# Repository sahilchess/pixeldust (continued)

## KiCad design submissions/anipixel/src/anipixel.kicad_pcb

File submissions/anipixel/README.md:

---
name: "Chengyin Yao"
slack_id: "U07EQJY9YDD"
github_handle: "@cheyao"
tutorial: # Link to the tutorial if you used one, including the default guide
wokwi: https://wokwi.com/projects/428567150311352321
---

# Anipixel!

I'm calling it anipixel because why not lol.

Wokwi sim works: [https://wokwi.com/projects/428567150311352321](https://wokwi.com/projects/428567150311352321)

This was a nice kicad project, speedran it! Was super easy

Replace the wokwi link below with yours

⚠️ I can't smd solder, so I would need a soldering station

<!-- Example: -->

| Comment           | Quantity | LCSC     | Cost   |
|-------------------|----------|----------|--------|
| 10uF              | 4        | C15850   | 0.01$ |
| 100nF             | 9        | C49678   | 0.45$ |
| USB receptacle    | 1        | C3020560 | 1.09$ |
| Inductor 2.2uF    | 1        | C135262  | 0.51$ |
| 100  resistor     | 1        | C105577  | 0.21$ |
| 5.1k resistor     | 2        | C2930296 | 0.14$ |
| TPS63001          | 1        | C28060   | 2.72$ |
| WS2812B           | 8        |          | |
| ESP32-WROOM-32E   | 1        |          | |

Would also need $ to cover shipping please!

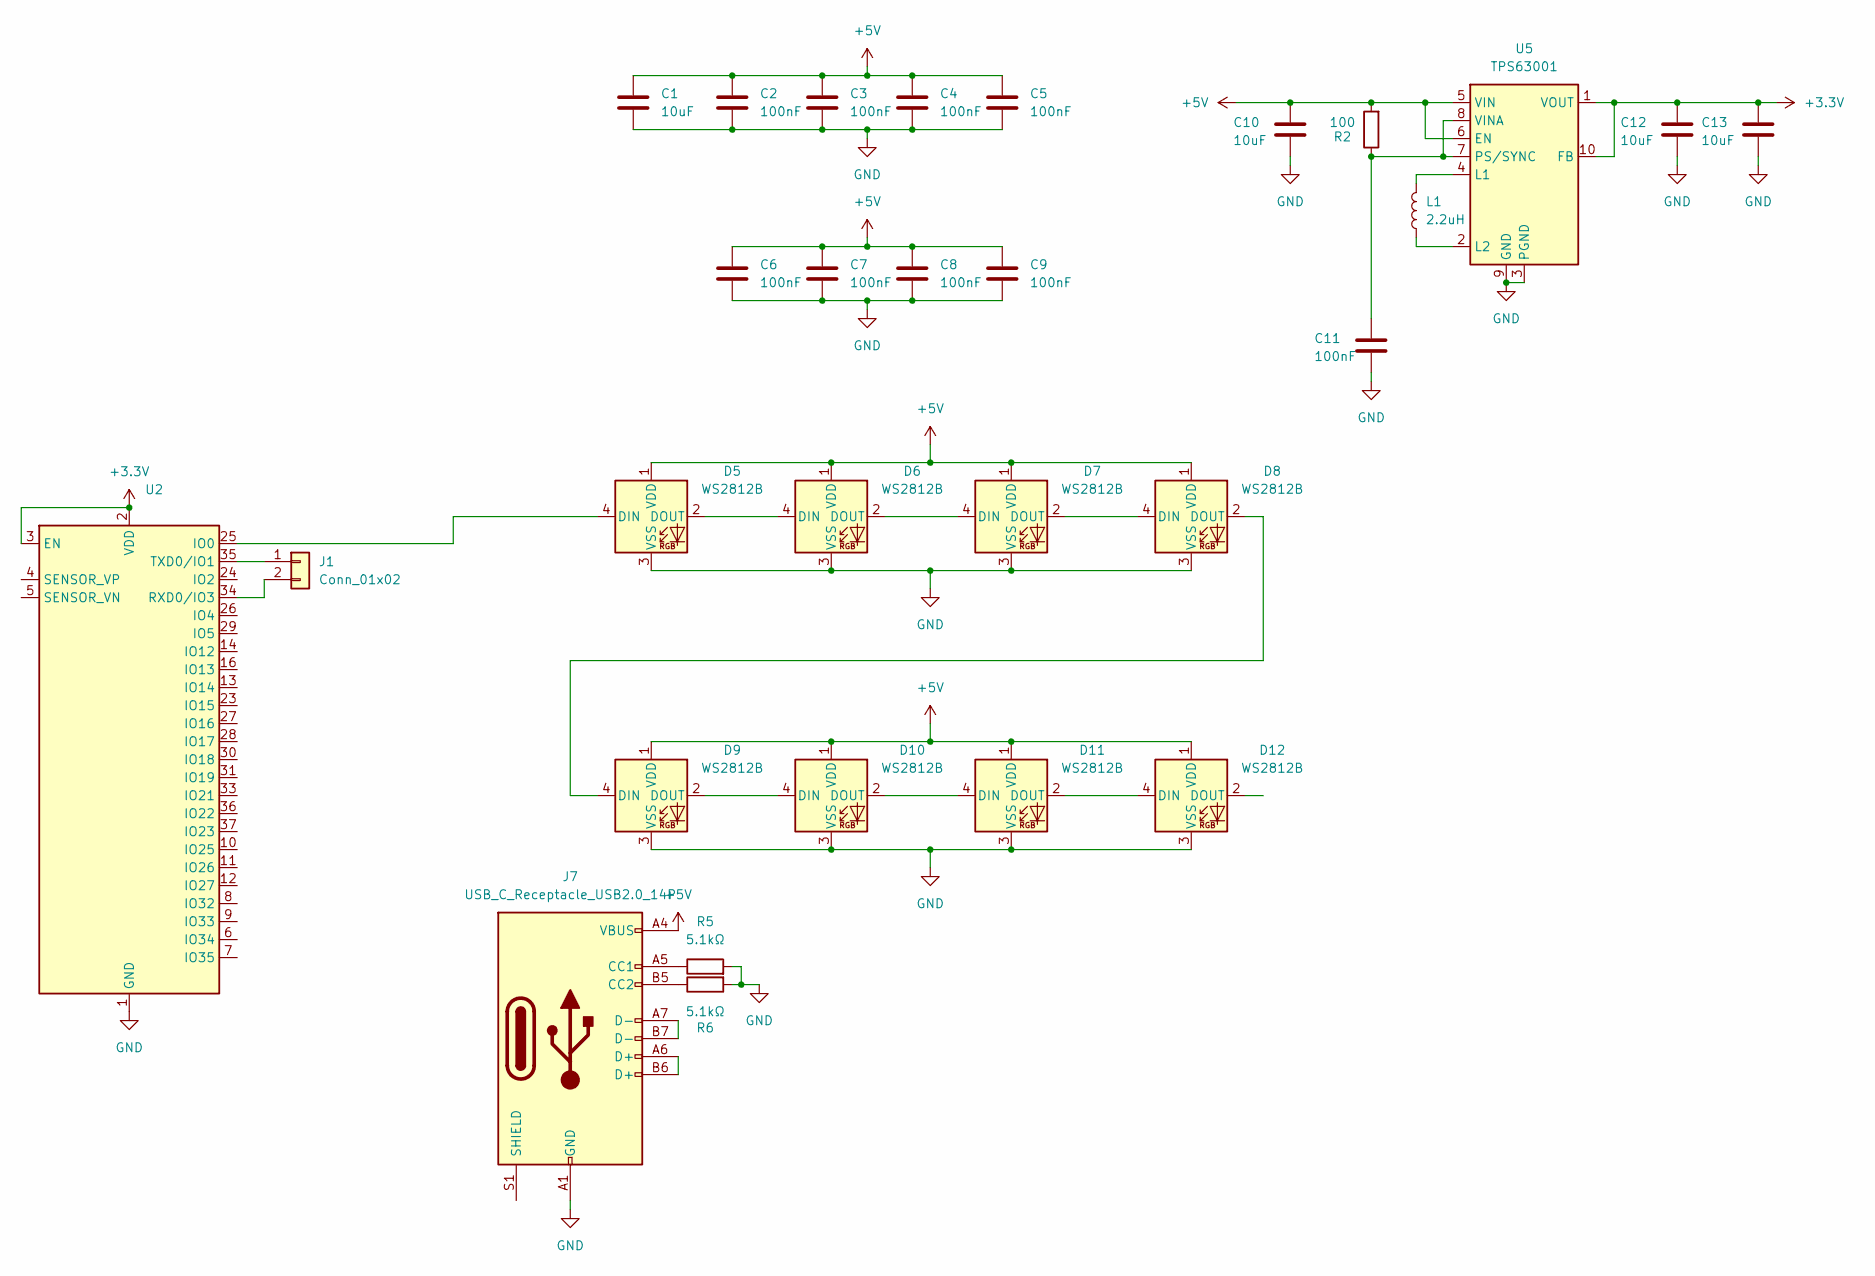
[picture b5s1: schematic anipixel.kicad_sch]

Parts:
C1, C10, C12, C13: 10uF; C_0805_2012Metric_Pad1.18x1.45mm_HandSolder
C2, C3, C4, C5, C6, C7, C8, C9, C11: 100nF; C_0805_2012Metric_Pad1.18x1.45mm_HandSolder
D5, D6, D7, D8, D9, D10, D11, D12: WS2812B; LED_WS2812B_PLCC4_5.0x5.0mm_P3.2mm
J1: Conn_01x02; PinHeader_1x02_P2.54mm_Vertical
J7: USB_C_Receptacle_USB2.0_14P; USB_C_Receptacle_GCT_USB4105-xx-A_16P_TopMnt_Horizontal
L1: 2.2uH; NR3015T2R2M
R2: 100; R_0805_2012Metric_Pad1.20x1.40mm_HandSolder
R5, R6: 5.1kΩ; R_0805_2012Metric_Pad1.20x1.40mm_HandSolder
U2: ESP32-WROOM-32E; ESP32-WROOM-32D
U5: TPS63001; Texas_DRC0010J_ThermalVias

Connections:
+3.3V: C12.1, C13.1, U2.2 (VDD), U2.3 (EN), U5.1 (VOUT), U5.10 (FB)
+5V: C1.1, C2.1, C3.1, C4.1, C5.1, C6.1, C7.1, C8.1, C9.1, C10.1, D5.1 (VDD), D6.1 (VDD), D7.1 (VDD), D8.1 (VDD), D9.1 (VDD), D10.1 (VDD), D11.1 (VDD), D12.1 (VDD), J7.A4 (VBUS), J7.A9 (VBUS), J7.B4 (VBUS), J7.B9 (VBUS), R2.2, U5.5 (VIN), U5.6 (EN)
GND: C1.2, C2.2, C3.2, C4.2, C5.2, C6.2, C7.2, C8.2, C9.2, C10.2, C11.2, C12.2, C13.2, D5.3 (VSS), D6.3 (VSS), D7.3 (VSS), D8.3 (VSS), D9.3 (VSS), D10.3 (VSS), D11.3 (VSS), D12.3 (VSS), J7.A1 (GND), J7.A12 (GND), J7.B1 (GND), J7.B12 (GND), R5.2, R6.2, U2.1 (GND), U2.15 (GND), U2.38 (GND), U2.39 (GND), U5.3 (PGND), U5.9 (GND), U5.11 (PGND)
unnamed: D5.4 (DIN), U2.25 (IO0)
unnamed: D5.2 (DOUT), D6.4 (DIN)
unnamed: D6.2 (DOUT), D7.4 (DIN)
unnamed: D7.2 (DOUT), D8.4 (DIN)
unnamed: D8.2 (DOUT), D9.4 (DIN)
unnamed: D9.2 (DOUT), D10.4 (DIN)
unnamed: D10.2 (DOUT), D11.4 (DIN)
unnamed: D11.2 (DOUT), D12.4 (DIN)
unnamed: J1.1, U2.35 (TXD0/IO1)
unnamed: J1.2, U2.34 (RXD0/IO3)
unnamed: J7.A5 (CC1), R5.1
unnamed: J7.B5 (CC2), R6.1
unnamed: J7.A6 (D+), J7.B6 (D+)
unnamed: J7.A7 (D-), J7.B7 (D-)
unnamed: L1.2, U5.4 (L1)
unnamed: L1.1, U5.2 (L2)
unnamed: C11.1, R2.1, U5.7 (PS/SYNC), U5.8 (VINA)

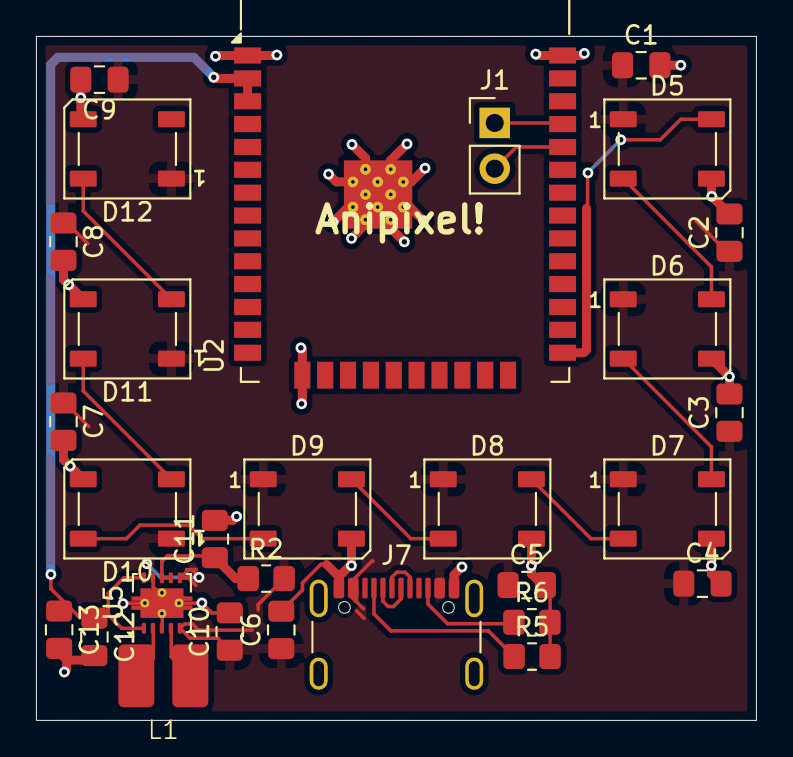
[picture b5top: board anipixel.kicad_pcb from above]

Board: 2 copper layers, 40.0 x 38.0 mm, 29 parts (0 on the bottom side), 20 nets.

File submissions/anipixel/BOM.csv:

Designator,Footprint,Quantity,Value,LCSC Part #
C1,0805,1,10u,
"C10, C12, C13",0805,3,10uF,
C11,0805,1,0.1uF,
"C2, C3, C4, C5, C6, C7, C8, C9",0805,8,100n,
"D10, D11, D12, D5, D6, D7, D8, D9",LED_WS2812B_PLCC4_5.0x5.0mm_P3.2mm,8,WS2812B,
J7,USB_C_Receptacle_GCT_USB4105-xx-A_16P_TopMnt_Horizontal,1,USB_C_Receptacle_USB2.0_14P,
L1,NR3015T2R2M,1,2.2uH,
R2,0805,1,100,
"R5, R6",0805,2,5.1kΩ,
U2,ESP32-WROOM-32D,1,ESP32-WROOM-32E,
U5,Texas_DRC0010J_ThermalVias,1,TPS63001,

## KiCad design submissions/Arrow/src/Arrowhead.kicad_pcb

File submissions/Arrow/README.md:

---
name: "SUKHDEEP SOMAL"
slack_id: "T0266FRGM"
github_handle: "@TwistedMiraculous"

wokwi: # Link to the Wokwi project
---

# Arrow head trinket

Wokwi link: [https://wokwi.com/projects/428801189855389697](https://wokwi.com/projects/428801189855389697)

Describe your board in 2-3 sentences. What are you making? What will it do?
I have made an led charm to make it either into a lightup bracelet, keychain, or a necklace. I will try to make a case for it but for now I want to keep it as it is, to show off that I made something.

A simplified BOM table

| Comment           | Footprint                                      | Quantity | LCSC     | Cost   |
|-------------------|------------------------------------------------|----------|----------|--------|
| 100uF             | Capacitor_SMD:CP_Elec_6.3x7.7                  | 1        | C15008   | 0.0682$|
| 0.1uF             | Capacitor_SMD:C_0603_1608Metric                | 7        | C1538    | 0.0011$|
| SK6812MINI        | LED_SMD:LED_SK6812MINI_PLCC4_3.5x3.5mm_P1.75mm | 8        | C1538    | 0.0726$|
| 330Ω              | Resistor_SMD:R_0402_1005Metric                 | 1        | C25091   | 0.0006$|
| XIAO-RP2040-DIP   | XIAO-RP2040-DIP                                | 1        |          | $5-8   |

Tell us a little bit about your design process. What were some challenges? What helped?

Some images of your design (make sure to include both the PCB and Schematic!):
,

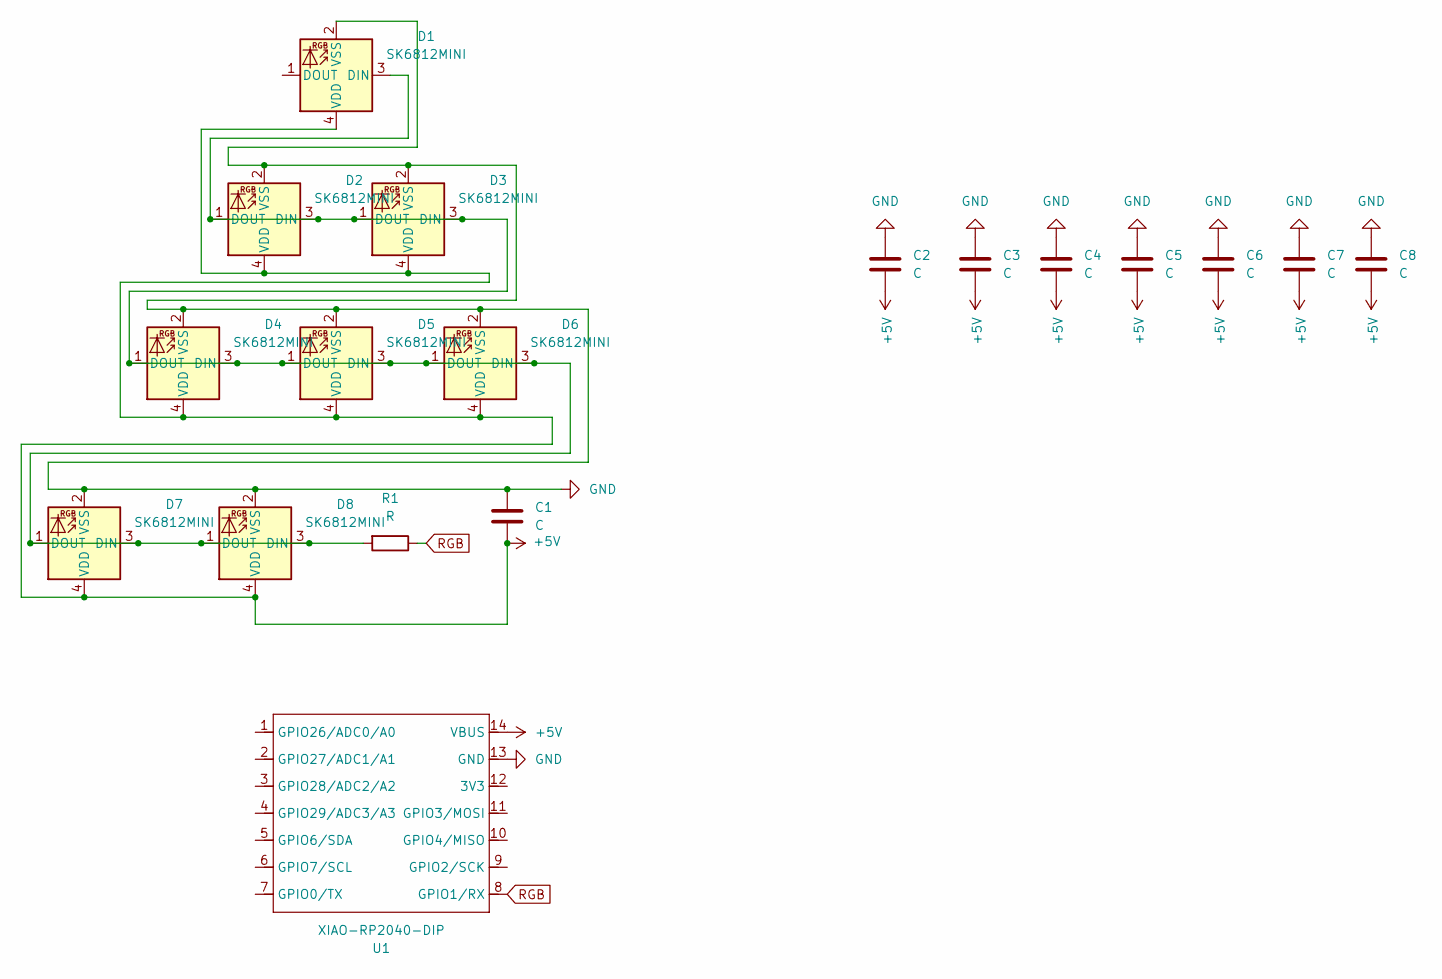
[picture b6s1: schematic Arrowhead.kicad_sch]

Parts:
C1: C; CP_Elec_6.3x7.7
C2, C3, C4, C5, C6, C7, C8: C; C_0603_1608Metric
D1, D2, D3, D4, D5, D6, D7, D8: SK6812MINI; LED_SK6812MINI_PLCC4_3.5x3.5mm_P1.75mm
R1: R; R_0402_1005Metric
U1: XIAO-RP2040-DIP

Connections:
+5V: C1.2, C2.2, C3.2, C4.2, C5.2, C6.2, C7.2, C8.2, D1.4 (VDD), D2.4 (VDD), D3.4 (VDD), D4.4 (VDD), D5.4 (VDD), D6.4 (VDD), D7.4 (VDD), D8.4 (VDD), U1.14 (VBUS)
GND: C1.1, C2.1, C3.1, C4.1, C5.1, C6.1, C7.1, C8.1, D1.2 (VSS), D2.2 (VSS), D3.2 (VSS), D4.2 (VSS), D5.2 (VSS), D6.2 (VSS), D7.2 (VSS), D8.2 (VSS), U1.13 (GND)
unnamed: D1.3 (DIN), D2.1 (DOUT), D2.3 (DIN), D3.1 (DOUT), D3.3 (DIN), D4.1 (DOUT), D4.3 (DIN), D5.1 (DOUT), D5.3 (DIN), D6.1 (DOUT), D6.3 (DIN), D7.1 (DOUT), D7.3 (DIN), D8.1 (DOUT), D8.3 (DIN), R1.2
RGB: R1.1, U1.8 (GPIO1/RX)

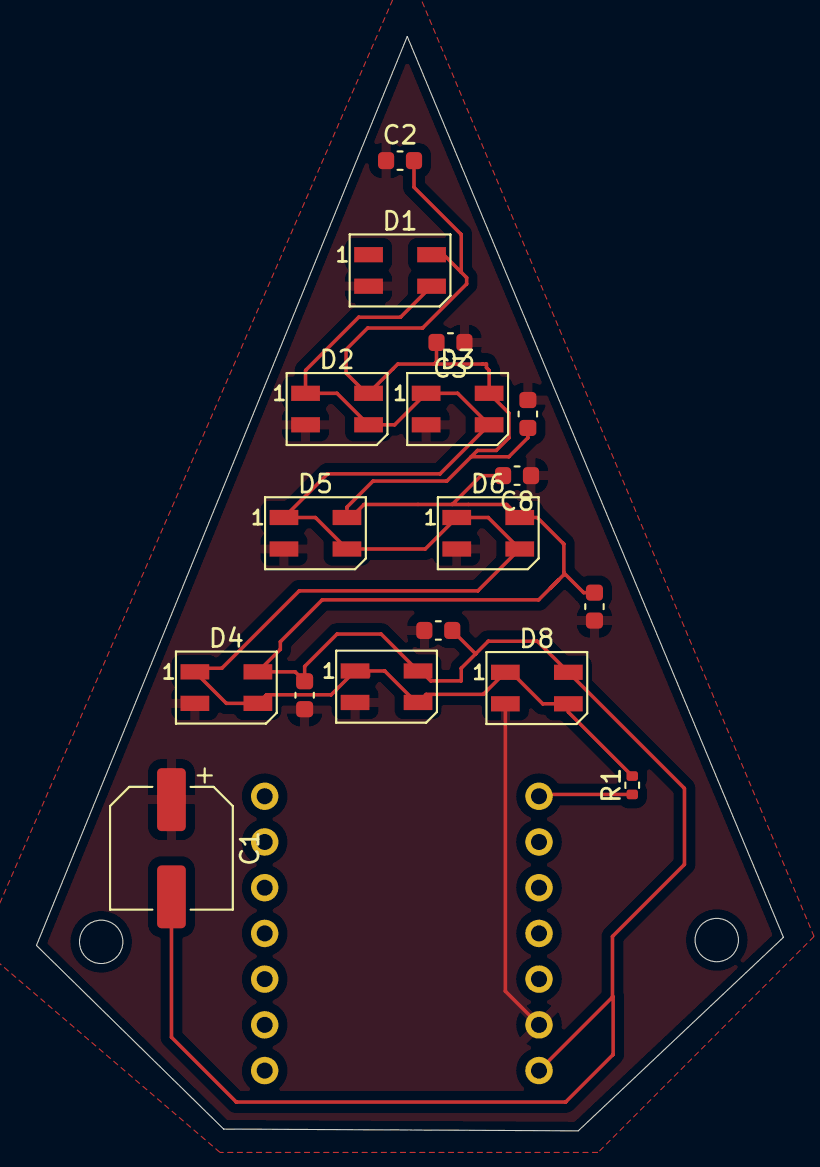
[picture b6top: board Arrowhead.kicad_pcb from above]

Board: 2 copper layers, 41.5 x 60.8 mm, 18 parts (1 on the bottom side), 4 nets.

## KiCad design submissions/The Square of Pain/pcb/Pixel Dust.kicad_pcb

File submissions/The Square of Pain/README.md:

# The Square of Pain

Jayson's slack ID: U085B15J7QW

Wokwi Link: https://wokwi.com/projects/427945974569788417
# Images

# PCB

# Schematic

# Model

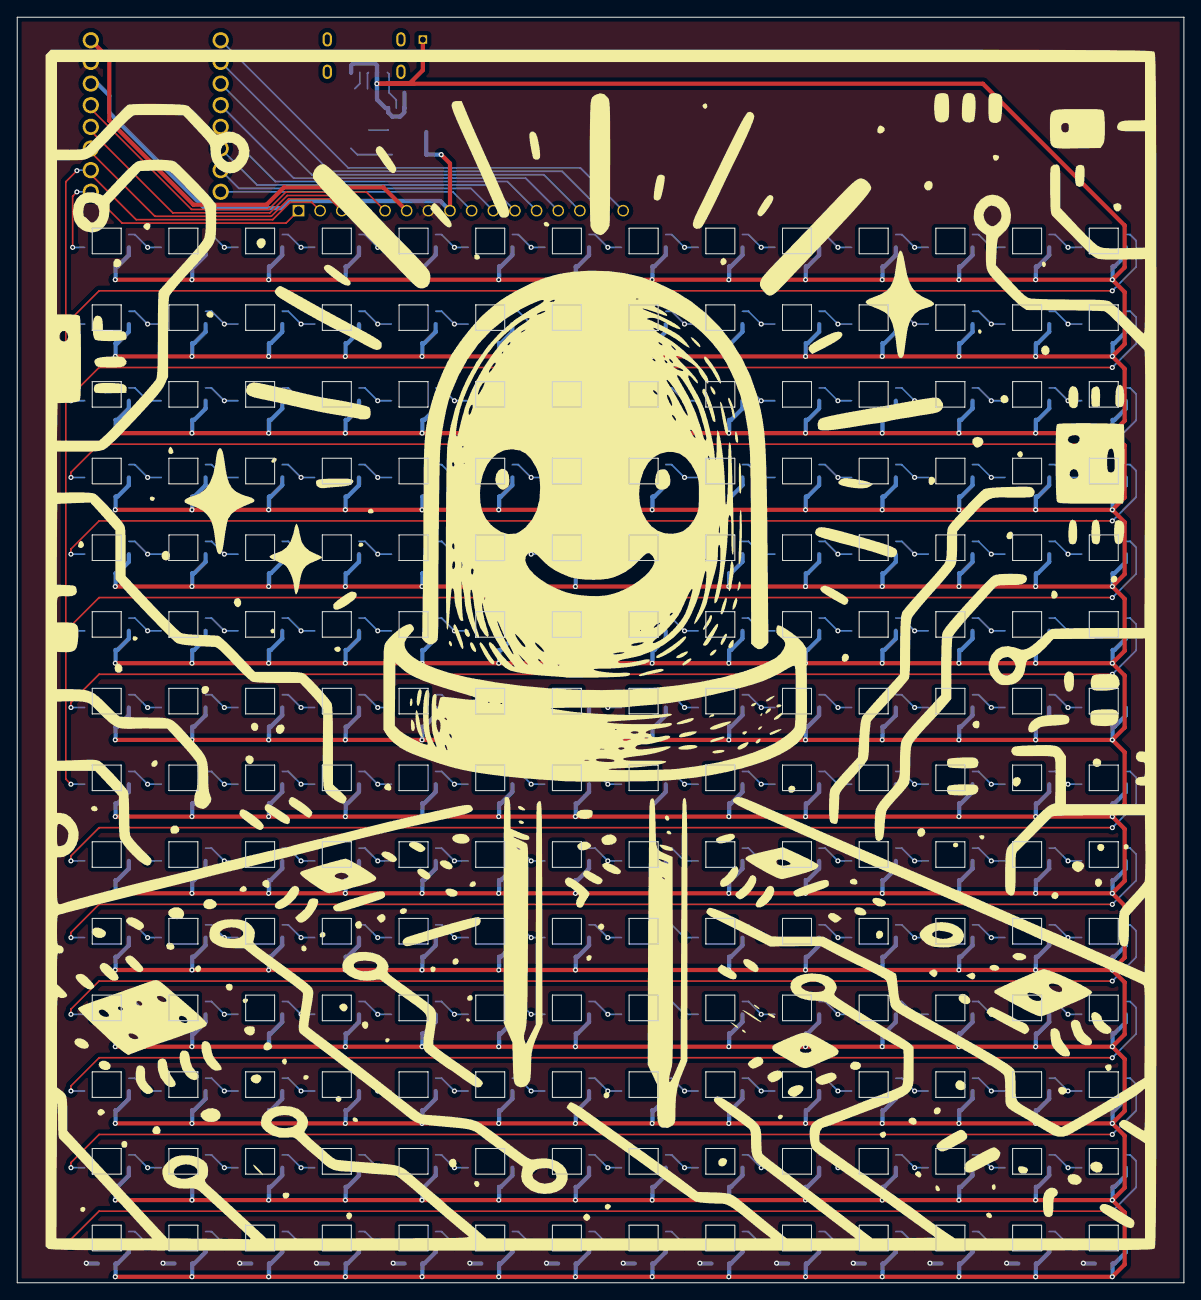
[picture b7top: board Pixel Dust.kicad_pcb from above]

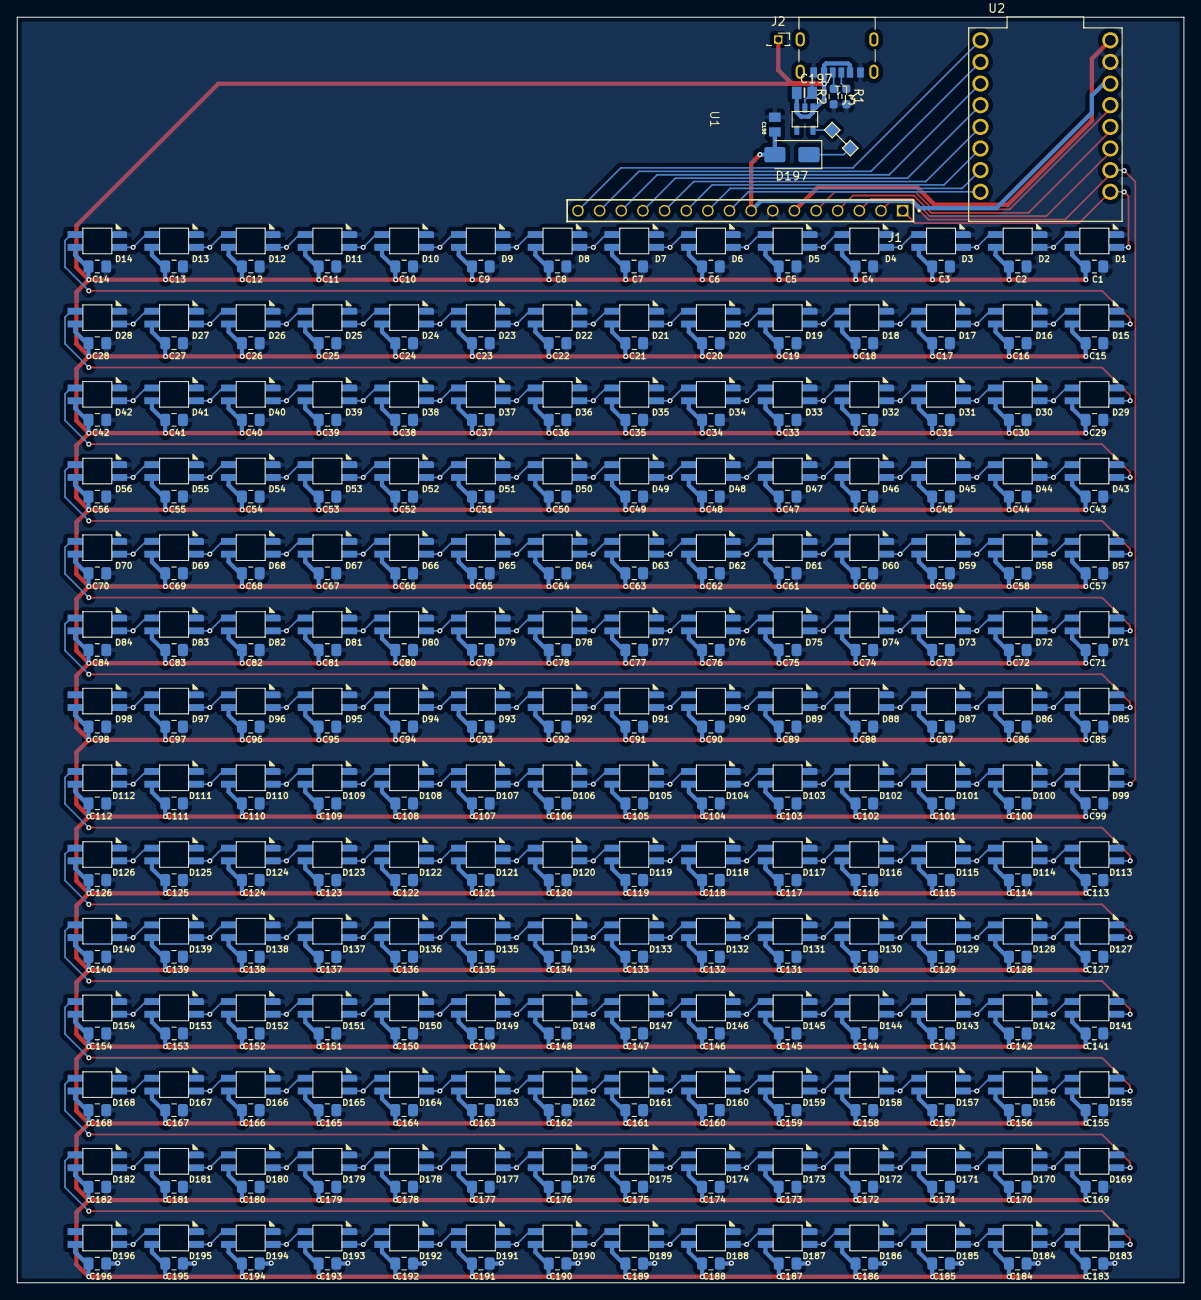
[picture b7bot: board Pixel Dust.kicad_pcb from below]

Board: 2 copper layers, 136.9 x 148.5 mm, 403 parts (403 on the bottom side), 215 nets.

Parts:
C1, C2, C3, C4, C5, C6, C7, C8, C9, C10, C11, C12, C13, C14, C15, C16, C17, C18, C19, C20, C21, C22, C23, C24, C25, C26, C27, C28, C29, C30, C31, C32, C33, C34, C35, C36, C37, C38, C39, C40, C41, C42, C43, C44, C45, C46, C47, C48, C49, C50, C51, C52, C53, C54, C55, C56, C57, C58, C59, C60, C61, C62, C63, C64, C65, C66, C67, C68, C69, C70, C71, C72, C73, C74, C75, C76, C77, C78, C79, C80, C81, C82, C83, C84, C85, C86, C87, C88, C89, C90, C91, C92, C93, C94, C95, C96, C97, C98, C99, C100, C101, C102, C103, C104, C105, C106, C107, C108, C109, C110, C111, C112, C113, C114, C115, C116, C117, C118, C119, C120, C121, C122, C123, C124, C125, C126, C127, C128, C129, C130, C131, C132, C133, C134, C135, C136, C137, C138, C139, C140, C141, C142, C143, C144, C145, C146, C147, C148, C149, C150, C151, C152, C153, C154, C155, C156, C157, C158, C159, C160, C161, C162, C163, C164, C165, C166, C167, C168, C169, C170, C171, C172, C173, C174, C175, C176, C177, C178, C179, C180, C181, C182, C183, C184, C185, C186, C187, C188, C189, C190, C191, C192, C193, C194, C195, C196: C; C_0805_2012Metric_Pad1.18x1.45mm_HandSolder
C197: 4.7 uF; CAPC2012X140N
C198: 10 uF; CAPC2012X135N
D1, D2, D3, D4, D5, D6, D7, D8, D9, D10, D11, D12, D13, D14, D15, D16, D17, D18, D19, D20, D21, D22, D23, D24, D25, D26, D27, D28, D29, D30, D31, D32, D33, D34, D35, D36, D37, D38, D39, D40, D41, D42, D43, D44, D45, D46, D47, D48, D49, D50, D51, D52, D53, D54, D55, D56, D57, D58, D59, D60, D61, D62, D63, D64, D65, D66, D67, D68, D69, D70, D71, D72, D73, D74, D75, D76, D77, D78, D79, D80, D81, D82, D83, D84, D85, D86, D87, D88, D89, D90, D91, D92, D93, D94, D95, D96, D97, D98, D99, D100, D101, D102, D103, D104, D105, D106, D107, D108, D109, D110, D111, D112, D113, D114, D115, D116, D117, D118, D119, D120, D121, D122, D123, D124, D125, D126, D127, D128, D129, D130, D131, D132, D133, D134, D135, D136, D137, D138, D139, D140, D141, D142, D143, D144, D145, D146, D147, D148, D149, D150, D151, D152, D153, D154, D155, D156, D157, D158, D159, D160, D161, D162, D163, D164, D165, D166, D167, D168, D169, D170, D171, D172, D173, D174, D175, D176, D177, D178, D179, D180, D181, D182, D183, D184, D185, D186, D187, D188, D189, D190, D191, D192, D193, D194, D195, D196: SK6812MINI; SK6812MINI-E
D197: SS14; D_SMA
J1: TSW-116-08-T-S-LL; SAMTEC_TSW-116-08-T-S-LL
J2: Conn_01x01_Socket; PinSocket_1x01_P1.27mm_Vertical
J3: USB_C_Receptacle_PowerOnly_6P; SAMESKY_UJC-H-G-SMT-2-P6-TR
L1: 2.2 uH; CDRH2D14NP-2R2NC
R1, R2: 5.1kΩ; R_0603_1608Metric_Pad0.98x0.95mm_HandSolder
U1: DC-DC_Converter
U2: ESP32-C3_SUPERMINI_TH; MODULE_ESP32-C3_SUPERMINI

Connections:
5V: J1.06, U2.5V
5in: C1.1, C2.1, C3.1, C4.1, C5.1, C6.1, C7.1, C8.1, C9.1, C10.1, C11.1, C12.1, C13.1, C14.1, C15.1, C16.1, C17.1, C18.1, C19.1, C20.1, C21.1, C22.1, C23.1, C24.1, C25.1, C26.1, C27.1, C28.1, C29.1, C30.1, C31.1, C32.1, C33.1, C34.1, C35.1, C36.1, C37.1, C38.1, C39.1, C40.1, C41.1, C42.1, C43.1, C44.1, C45.1, C46.1, C47.1, C48.1, C49.1, C50.1, C51.1, C52.1, C53.1, C54.1, C55.1, C56.1, C57.1, C58.1, C59.1, C60.1, C61.1, C62.1, C63.1, C64.1, C65.1, C66.1, C67.1, C68.1, C69.1, C70.1, C71.1, C72.1, C73.1, C74.1, C75.1, C76.1, C77.1, C78.1, C79.1, C80.1, C81.1, C82.1, C83.1, C84.1, C85.1, C86.1, C87.1, C88.1, C89.1, C90.1, C91.1, C92.1, C93.1, C94.1, C95.1, C96.1, C97.1, C98.1, C99.1, C100.1, C101.1, C102.1, C103.1, C104.1, C105.1, C106.1, C107.1, C108.1, C109.1, C110.1, C111.1, C112.1, C113.1, C114.1, C115.1, C116.1, C117.1, C118.1, C119.1, C120.1, C121.1, C122.1, C123.1, C124.1, C125.1, C126.1, C127.1, C128.1, C129.1, C130.1, C131.1, C132.1, C133.1, C134.1, C135.1, C136.1, C137.1, C138.1, C139.1, C140.1, C141.1, C142.1, C143.1, C144.1, C145.1, C146.1, C147.1, C148.1, C149.1, C150.1, C151.1, C152.1, C153.1, C154.1, C155.1, C156.1, C157.1, C158.1, C159.1, C160.1, C161.1, C162.1, C163.1, C164.1, C165.1, C166.1, C167.1, C168.1, C169.1, C170.1, C171.1, C172.1, C173.1, C174.1, C175.1, C176.1, C177.1, C178.1, C179.1, C180.1, C181.1, C182.1, C183.1, C184.1, C185.1, C186.1, C187.1, C188.1, C189.1, C190.1, C191.1, C192.1, C193.1, C194.1, C195.1, C196.1, C197.1, D1.4 (VDD), D2.4 (VDD), D3.4 (VDD), D4.4 (VDD), D5.4 (VDD), D6.4 (VDD), D7.4 (VDD), D8.4 (VDD), D9.4 (VDD), D10.4 (VDD), D11.4 (VDD), D12.4 (VDD), D13.4 (VDD), D14.4 (VDD), D15.4 (VDD), D16.4 (VDD), D17.4 (VDD), D18.4 (VDD), D19.4 (VDD), D20.4 (VDD), D21.4 (VDD), D22.4 (VDD), D23.4 (VDD), D24.4 (VDD), D25.4 (VDD), D26.4 (VDD), D27.4 (VDD), D28.4 (VDD), D29.4 (VDD), D30.4 (VDD), D31.4 (VDD), D32.4 (VDD), D33.4 (VDD), D34.4 (VDD), D35.4 (VDD), D36.4 (VDD), D37.4 (VDD), D38.4 (VDD), D39.4 (VDD), D40.4 (VDD), D41.4 (VDD), D42.4 (VDD), D43.4 (VDD), D44.4 (VDD), D45.4 (VDD), D46.4 (VDD), D47.4 (VDD), D48.4 (VDD), D49.4 (VDD), D50.4 (VDD), D51.4 (VDD), D52.4 (VDD), D53.4 (VDD), D54.4 (VDD), D55.4 (VDD), D56.4 (VDD), D57.4 (VDD), D58.4 (VDD), D59.4 (VDD), D60.4 (VDD), D61.4 (VDD), D62.4 (VDD), D63.4 (VDD), D64.4 (VDD), D65.4 (VDD), D66.4 (VDD), D67.4 (VDD), D68.4 (VDD), D69.4 (VDD), D70.4 (VDD), D71.4 (VDD), D72.4 (VDD), D73.4 (VDD), D74.4 (VDD), D75.4 (VDD), D76.4 (VDD), D77.4 (VDD), D78.4 (VDD), D79.4 (VDD), D80.4 (VDD), D81.4 (VDD), D82.4 (VDD), D83.4 (VDD), D84.4 (VDD), D85.4 (VDD), D86.4 (VDD), D87.4 (VDD), D88.4 (VDD), D89.4 (VDD), D90.4 (VDD)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
+3.3V: C198.1, D197.2 (A), J1.08, U2.3.3 (3V3)
GND: C1.2, C2.2, C3.2, C4.2, C5.2, C6.2, C7.2, C8.2, C9.2, C10.2, C11.2, C12.2, C13.2, C14.2, C15.2, C16.2, C17.2, C18.2, C19.2, C20.2, C21.2, C22.2, C23.2, C24.2, C25.2, C26.2, C27.2, C28.2, C29.2, C30.2, C31.2, C32.2, C33.2, C34.2, C35.2, C36.2, C37.2, C38.2, C39.2, C40.2, C41.2, C42.2, C43.2, C44.2, C45.2, C46.2, C47.2, C48.2, C49.2, C50.2, C51.2, C52.2, C53.2, C54.2, C55.2, C56.2, C57.2, C58.2, C59.2, C60.2, C61.2, C62.2, C63.2, C64.2, C65.2, C66.2, C67.2, C68.2, C69.2, C70.2, C71.2, C72.2, C73.2, C74.2, C75.2, C76.2, C77.2, C78.2, C79.2, C80.2, C81.2, C82.2, C83.2, C84.2, C85.2, C86.2, C87.2, C88.2, C89.2, C90.2, C91.2, C92.2, C93.2, C94.2, C95.2, C96.2, C97.2, C98.2, C99.2, C100.2, C101.2, C102.2, C103.2, C104.2, C105.2, C106.2, C107.2, C108.2, C109.2, C110.2, C111.2, C112.2, C113.2, C114.2, C115.2, C116.2, C117.2, C118.2, C119.2, C120.2, C121.2, C122.2, C123.2, C124.2, C125.2, C126.2, C127.2, C128.2, C129.2, C130.2, C131.2, C132.2, C133.2, C134.2, C135.2, C136.2, C137.2, C138.2, C139.2, C140.2, C141.2, C142.2, C143.2, C144.2, C145.2, C146.2, C147.2, C148.2, C149.2, C150.2, C151.2, C152.2, C153.2, C154.2, C155.2, C156.2, C157.2, C158.2, C159.2, C160.2, C161.2, C162.2, C163.2, C164.2, C165.2, C166.2, C167.2, C168.2, C169.2, C170.2, C171.2, C172.2, C173.2, C174.2, C175.2, C176.2, C177.2, C178.2, C179.2, C180.2, C181.2, C182.2, C183.2, C184.2, C185.2, C186.2, C187.2, C188.2, C189.2, C190.2, C191.2, C192.2, C193.2, C194.2, C195.2, C196.2, C197.2, C198.2, D1.2 (VSS), D2.2 (VSS), D3.2 (VSS), D4.2 (VSS), D5.2 (VSS), D6.2 (VSS), D7.2 (VSS), D8.2 (VSS), D9.2 (VSS), D10.2 (VSS), D11.2 (VSS), D12.2 (VSS), D13.2 (VSS), D14.2 (VSS), D15.2 (VSS), D16.2 (VSS), D17.2 (VSS), D18.2 (VSS), D19.2 (VSS), D20.2 (VSS), D21.2 (VSS), D22.2 (VSS), D23.2 (VSS), D24.2 (VSS), D25.2 (VSS), D26.2 (VSS), D27.2 (VSS), D28.2 (VSS), D29.2 (VSS), D30.2 (VSS), D31.2 (VSS), D32.2 (VSS), D33.2 (VSS), D34.2 (VSS), D35.2 (VSS), D36.2 (VSS), D37.2 (VSS), D38.2 (VSS), D39.2 (VSS), D40.2 (VSS), D41.2 (VSS), D42.2 (VSS), D43.2 (VSS), D44.2 (VSS), D45.2 (VSS), D46.2 (VSS), D47.2 (VSS), D48.2 (VSS), D49.2 (VSS), D50.2 (VSS), D51.2 (VSS), D52.2 (VSS), D53.2 (VSS), D54.2 (VSS), D55.2 (VSS), D56.2 (VSS), D57.2 (VSS), D58.2 (VSS), D59.2 (VSS), D60.2 (VSS), D61.2 (VSS), D62.2 (VSS), D63.2 (VSS), D64.2 (VSS), D65.2 (VSS), D66.2 (VSS), D67.2 (VSS), D68.2 (VSS), D69.2 (VSS), D70.2 (VSS), D71.2 (VSS), D72.2 (VSS), D73.2 (VSS), D74.2 (VSS), D75.2 (VSS), D76.2 (VSS), D77.2 (VSS), D78.2 (VSS), D79.2 (VSS), D80.2 (VSS), D81.2 (VSS), D82.2 (VSS), D83.2 (VSS), D84.2 (VSS), D85.2 (VSS), D86.2 (VSS), D87.2 (VSS), D88.2 (VSS), D89.2 (VSS)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
GPIO0: D1.3 (DIN), J1.01, U2.0 (GPIO0)
GPIO1: D99.3 (DIN), J1.02, U2.1 (GPIO1)
GPIO2: J1.03, U2.2 (GPIO2)
GPIO3: J1.04, U2.3 (GPIO3)
GPIO4: J1.05, U2.4 (GPIO4)
GPIO5: J1.16, U2.5 (GPIO5)
GPIO6: J1.15, U2.6 (GPIO6)
GPIO7: J1.14, U2.7 (GPIO7)
GPIO8: J1.13, U2.8 (GPIO8)
GPIO9: J1.12, U2.9 (GPIO9)
GPIO10: J1.11, U2.10 (GPIO10)
GPIO20: J1.10, U2.20 (GPIO20)
GPIO21: J1.09, U2.21 (GPIO21)
unnamed: D1.1 (DOUT), D2.3 (DIN)
unnamed: D2.1 (DOUT), D3.3 (DIN)
unnamed: D3.1 (DOUT), D4.3 (DIN)
unnamed: D4.1 (DOUT), D5.3 (DIN)
unnamed: D5.1 (DOUT), D6.3 (DIN)
unnamed: D6.1 (DOUT), D7.3 (DIN)
unnamed: D7.1 (DOUT), D8.3 (DIN)
unnamed: D8.1 (DOUT), D9.3 (DIN)
unnamed: D9.1 (DOUT), D10.3 (DIN)
unnamed: D10.1 (DOUT), D11.3 (DIN)
unnamed: D11.1 (DOUT), D12.3 (DIN)
unnamed: D12.1 (DOUT), D13.3 (DIN)
unnamed: D13.1 (DOUT), D14.3 (DIN)
unnamed: D14.1 (DOUT), D15.3 (DIN)
unnamed: D15.1 (DOUT), D16.3 (DIN)
unnamed: D16.1 (DOUT), D17.3 (DIN)
unnamed: D17.1 (DOUT), D18.3 (DIN)
unnamed: D18.1 (DOUT), D19.3 (DIN)
unnamed: D19.1 (DOUT), D20.3 (DIN)
unnamed: D20.1 (DOUT), D21.3 (DIN)
unnamed: D21.1 (DOUT), D22.3 (DIN)
unnamed: D22.1 (DOUT), D23.3 (DIN)
unnamed: D23.1 (DOUT), D24.3 (DIN)
unnamed: D24.1 (DOUT), D25.3 (DIN)
unnamed: D25.1 (DOUT), D26.3 (DIN)
unnamed: D26.1 (DOUT), D27.3 (DIN)
unnamed: D27.1 (DOUT), D28.3 (DIN)
unnamed: D28.1 (DOUT), D29.3 (DIN)
unnamed: D29.1 (DOUT), D30.3 (DIN)
unnamed: D30.1 (DOUT), D31.3 (DIN)
unnamed: D31.1 (DOUT), D32.3 (DIN)
unnamed: D32.1 (DOUT), D33.3 (DIN)
unnamed: D33.1 (DOUT), D34.3 (DIN)
unnamed: D34.1 (DOUT), D35.3 (DIN)
unnamed: D35.1 (DOUT), D36.3 (DIN)
unnamed: D36.1 (DOUT), D37.3 (DIN)
unnamed: D37.1 (DOUT), D38.3 (DIN)
unnamed: D38.1 (DOUT), D39.3 (DIN)
unnamed: D39.1 (DOUT), D40.3 (DIN)
unnamed: D40.1 (DOUT), D41.3 (DIN)
unnamed: D41.1 (DOUT), D42.3 (DIN)
unnamed: D42.1 (DOUT), D43.3 (DIN)
unnamed: D43.1 (DOUT), D44.3 (DIN)
unnamed: D44.1 (DOUT), D45.3 (DIN)
unnamed: D45.1 (DOUT), D46.3 (DIN)
unnamed: D46.1 (DOUT), D47.3 (DIN)
unnamed: D47.1 (DOUT), D48.3 (DIN)
unnamed: D48.1 (DOUT), D49.3 (DIN)
unnamed: D49.1 (DOUT), D50.3 (DIN)
unnamed: D50.1 (DOUT), D51.3 (DIN)
unnamed: D51.1 (DOUT), D52.3 (DIN)
unnamed: D52.1 (DOUT), D53.3 (DIN)
unnamed: D53.1 (DOUT), D54.3 (DIN)
unnamed: D54.1 (DOUT), D55.3 (DIN)
unnamed: D55.1 (DOUT), D56.3 (DIN)
unnamed: D56.1 (DOUT), D57.3 (DIN)
unnamed: D57.1 (DOUT), D58.3 (DIN)
unnamed: D58.1 (DOUT), D59.3 (DIN)
unnamed: D59.1 (DOUT), D60.3 (DIN)
unnamed: D60.1 (DOUT), D61.3 (DIN)
unnamed: D61.1 (DOUT), D62.3 (DIN)
unnamed: D62.1 (DOUT), D63.3 (DIN)
unnamed: D63.1 (DOUT), D64.3 (DIN)
unnamed: D64.1 (DOUT), D65.3 (DIN)
unnamed: D65.1 (DOUT), D66.3 (DIN)
unnamed: D66.1 (DOUT), D67.3 (DIN)
unnamed: D67.1 (DOUT), D68.3 (DIN)
unnamed: D68.1 (DOUT), D69.3 (DIN)
unnamed: D69.1 (DOUT), D70.3 (DIN)
unnamed: D70.1 (DOUT), D71.3 (DIN)
unnamed: D71.1 (DOUT), D72.3 (DIN)
unnamed: D72.1 (DOUT), D73.3 (DIN)
unnamed: D73.1 (DOUT), D74.3 (DIN)
unnamed: D74.1 (DOUT), D75.3 (DIN)
unnamed: D75.1 (DOUT), D76.3 (DIN)
unnamed: D76.1 (DOUT), D77.3 (DIN)
unnamed: D77.1 (DOUT), D78.3 (DIN)
unnamed: D78.1 (DOUT), D79.3 (DIN)
unnamed: D79.1 (DOUT), D80.3 (DIN)
unnamed: D80.1 (DOUT), D81.3 (DIN)
unnamed: D81.1 (DOUT), D82.3 (DIN)
unnamed: D82.1 (DOUT), D83.3 (DIN)
unnamed: D83.1 (DOUT), D84.3 (DIN)
unnamed: D84.1 (DOUT), D85.3 (DIN)
unnamed: D85.1 (DOUT), D86.3 (DIN)
unnamed: D86.1 (DOUT), D87.3 (DIN)
unnamed: D87.1 (DOUT), D88.3 (DIN)
unnamed: D88.1 (DOUT), D89.3 (DIN)
unnamed: D89.1 (DOUT), D90.3 (DIN)
unnamed: D90.1 (DOUT), D91.3 (DIN)
unnamed: D91.1 (DOUT), D92.3 (DIN)
unnamed: D92.1 (DOUT), D93.3 (DIN)
unnamed: D93.1 (DOUT), D94.3 (DIN)
unnamed: D94.1 (DOUT), D95.3 (DIN)
unnamed: D95.1 (DOUT), D96.3 (DIN)
unnamed: D96.1 (DOUT), D97.3 (DIN)
unnamed: D97.1 (DOUT), D98.3 (DIN)
unnamed: D99.1 (DOUT), D100.3 (DIN)
unnamed: D100.1 (DOUT), D101.3 (DIN)
unnamed: D101.1 (DOUT), D102.3 (DIN)
unnamed: D102.1 (DOUT), D103.3 (DIN)
unnamed: D103.1 (DOUT), D104.3 (DIN)
unnamed: D104.1 (DOUT), D105.3 (DIN)
unnamed: D105.1 (DOUT), D106.3 (DIN)
unnamed: D106.1 (DOUT), D107.3 (DIN)
unnamed: D107.1 (DOUT), D108.3 (DIN)
unnamed: D108.1 (DOUT), D109.3 (DIN)
unnamed: D109.1 (DOUT), D110.3 (DIN)
unnamed: D110.1 (DOUT), D111.3 (DIN)
unnamed: D111.1 (DOUT), D112.3 (DIN)
unnamed: D112.1 (DOUT), D113.3 (DIN)
unnamed: D113.1 (DOUT), D114.3 (DIN)
unnamed: D114.1 (DOUT), D115.3 (DIN)
unnamed: D115.1 (DOUT), D116.3 (DIN)
unnamed: D116.1 (DOUT), D117.3 (DIN)
unnamed: D117.1 (DOUT), D118.3 (DIN)
unnamed: D118.1 (DOUT), D119.3 (DIN)
unnamed: D119.1 (DOUT), D120.3 (DIN)
unnamed: D120.1 (DOUT), D121.3 (DIN)
unnamed: D121.1 (DOUT), D122.3 (DIN)
unnamed: D122.1 (DOUT), D123.3 (DIN)
unnamed: D123.1 (DOUT), D124.3 (DIN)
unnamed: D124.1 (DOUT), D125.3 (DIN)
unnamed: D125.1 (DOUT), D126.3 (DIN)
unnamed: D126.1 (DOUT), D127.3 (DIN)
unnamed: D127.1 (DOUT), D128.3 (DIN)
unnamed: D128.1 (DOUT), D129.3 (DIN)
unnamed: D129.1 (DOUT), D130.3 (DIN)
unnamed: D130.1 (DOUT), D131.3 (DIN)
unnamed: D131.1 (DOUT), D132.3 (DIN)
unnamed: D132.1 (DOUT), D133.3 (DIN)
unnamed: D133.1 (DOUT), D134.3 (DIN)
unnamed: D134.1 (DOUT), D135.3 (DIN)
unnamed: D135.1 (DOUT), D136.3 (DIN)
unnamed: D136.1 (DOUT), D137.3 (DIN)
unnamed: D137.1 (DOUT), D138.3 (DIN)
unnamed: D138.1 (DOUT), D139.3 (DIN)
unnamed: D139.1 (DOUT), D140.3 (DIN)
unnamed: D140.1 (DOUT), D141.3 (DIN)
unnamed: D141.1 (DOUT), D142.3 (DIN)
unnamed: D142.1 (DOUT), D143.3 (DIN)
unnamed: D143.1 (DOUT), D144.3 (DIN)
unnamed: D144.1 (DOUT), D145.3 (DIN)
unnamed: D145.1 (DOUT), D146.3 (DIN)
unnamed: D146.1 (DOUT), D147.3 (DIN)
unnamed: D147.1 (DOUT), D148.3 (DIN)
unnamed: D148.1 (DOUT), D149.3 (DIN)
unnamed: D149.1 (DOUT), D150.3 (DIN)
unnamed: D150.1 (DOUT), D151.3 (DIN)
unnamed: D151.1 (DOUT), D152.3 (DIN)
unnamed: D152.1 (DOUT), D153.3 (DIN)
unnamed: D153.1 (DOUT), D154.3 (DIN)
unnamed: D154.1 (DOUT), D155.3 (DIN)
unnamed: D155.1 (DOUT), D156.3 (DIN)
unnamed: D156.1 (DOUT), D157.3 (DIN)
unnamed: D157.1 (DOUT), D158.3 (DIN)
unnamed: D158.1 (DOUT), D159.3 (DIN)
unnamed: D159.1 (DOUT), D160.3 (DIN)
unnamed: D160.1 (DOUT), D161.3 (DIN)
unnamed: D161.1 (DOUT), D162.3 (DIN)
unnamed: D162.1 (DOUT), D163.3 (DIN)
unnamed: D163.1 (DOUT), D164.3 (DIN)
unnamed: D164.1 (DOUT), D165.3 (DIN)
unnamed: D165.1 (DOUT), D166.3 (DIN)
unnamed: D166.1 (DOUT), D167.3 (DIN)
unnamed: D167.1 (DOUT), D168.3 (DIN)
unnamed: D168.1 (DOUT), D169.3 (DIN)
unnamed: D169.1 (DOUT), D170.3 (DIN)
unnamed: D170.1 (DOUT), D171.3 (DIN)
unnamed: D171.1 (DOUT), D172.3 (DIN)
unnamed: D172.1 (DOUT), D173.3 (DIN)
unnamed: D173.1 (DOUT), D174.3 (DIN)
unnamed: D174.1 (DOUT), D175.3 (DIN)
unnamed: D175.1 (DOUT), D176.3 (DIN)
unnamed: D176.1 (DOUT), D177.3 (DIN)
unnamed: D177.1 (DOUT), D178.3 (DIN)
unnamed: D178.1 (DOUT), D179.3 (DIN)
unnamed: D179.1 (DOUT), D180.3 (DIN)
unnamed: D180.1 (DOUT), D181.3 (DIN)
unnamed: D181.1 (DOUT), D182.3 (DIN)
unnamed: D182.1 (DOUT), D183.3 (DIN)
unnamed: D183.1 (DOUT), D184.3 (DIN)
unnamed: D184.1 (DOUT), D185.3 (DIN)
unnamed: D185.1 (DOUT), D186.3 (DIN)
unnamed: D186.1 (DOUT), D187.3 (DIN)
unnamed: D187.1 (DOUT), D188.3 (DIN)
unnamed: D188.1 (DOUT), D189.3 (DIN)
unnamed: D189.1 (DOUT), D190.3 (DIN)
unnamed: D190.1 (DOUT), D191.3 (DIN)
unnamed: D191.1 (DOUT), D192.3 (DIN)
unnamed: D192.1 (DOUT), D193.3 (DIN)
unnamed: D193.1 (DOUT), D194.3 (DIN)
unnamed: D194.1 (DOUT), D195.3 (DIN)
unnamed: D195.1 (DOUT), D196.3 (DIN)
unnamed: D197.1 (K), L1.2
unnamed: J3.A5 (CC1), R1.1
unnamed: J3.B5 (CC2), R2.2
unnamed: L1.1, U1.5 (SW)

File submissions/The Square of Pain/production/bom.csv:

Designator,Footprint,Quantity,Value,LCSC Part #
"C1, C10, C100, C101, C102, C103, C104, C105, C106, C107, C108, C109, C11, C110, C111, C112, C113, C114, C115, C116, C117, C118, C119, C12, C120, C121, C122, C123, C124, C125, C126, C127, C128, C129, C13, C130, C131, C132, C133, C134, C135, C136, C137, C138, C139, C14, C140, C141, C142, C143, C144, C145, C146, C147, C148, C149, C15, C150, C151, C152, C153, C154, C155, C156, C157, C158, C159, C16, C160, C161, C162, C163, C164, C165, C166, C167, C168, C169, C17, C170, C171, C172, C173, C174, C175, C176, C177, C178, C179, C18, C180, C181, C182, C183, C184, C185, C186, C187, C188, C189, C19, C190, C191, C192, C193, C194, C195, C196, C2, C20, C21, C22, C23, C24, C25, C26, C27, C28, C29, C3, C30, C31, C32, C33, C34, C35, C36, C37, C38, C39, C4, C40, C41, C42, C43, C44, C45, C46, C47, C48, C49, C5, C50, C51, C52, C53, C54, C55, C56, C57, C58, C59, C6, C60, C61, C62, C63, C64, C65, C66, C67, C68, C69, C7, C70, C71, C72, C73, C74, C75, C76, C77, C78, C79, C8, C80, C81, C82, C83, C84, C85, C86, C87, C88, C89, C9, C90, C91, C92, C93, C94, C95, C96, C97, C98, C99",0805,196,C,
"D1, D10, D100, D101, D102, D103, D104, D105, D106, D107, D108, D109, D11, D110, D111, D112, D113, D114, D115, D116, D117, D118, D119, D12, D120, D121, D122, D123, D124, D125, D126, D127, D128, D129, D13, D130, D131, D132, D133, D134, D135, D136, D137, D138, D139, D14, D140, D141, D142, D143, D144, D145, D146, D147, D148, D149, D15, D150, D151, D152, D153, D154, D155, D156, D157, D158, D159, D16, D160, D161, D162, D163, D164, D165, D166, D167, D168, D169, D17, D170, D171, D172, D173, D174, D175, D176, D177, D178, D179, D18, D180, D181, D182, D183, D184, D185, D186, D187, D188, D189, D19, D190, D191, D192, D193, D194, D195, D196, D2, D20, D21, D22, D23, D24, D25, D26, D27, D28, D29, D3, D30, D31, D32, D33, D34, D35, D36, D37, D38, D39, D4, D40, D41, D42, D43, D44, D45, D46, D47, D48, D49, D5, D50, D51, D52, D53, D54, D55, D56, D57, D58, D59, D6, D60, D61, D62, D63, D64, D65, D66, D67, D68, D69, D7, D70, D71, D72, D73, D74, D75, D76, D77, D78, D79, D8, D80, D81, D82, D83, D84, D85, D86, D87, D88, D89, D9, D90, D91, D92, D93, D94, D95, D96, D97, D98, D99",SK6812MINI-E,196,SK6812MINI,
J1,SAMTEC_TSW-116-08-T-S-LL,1,TSW-116-08-T-S-LL,
J2,PinSocket_1x01_P1.27mm_Vertical,1,Conn_01x01_Socket,
J3,SAMESKY_UJC-H-G-SMT-2-P6-TR,1,USB_C_Receptacle_PowerOnly_6P,
"R1, R2",0603,2,5.1kΩ,
U2,MODULE_ESP32-C3_SUPERMINI,1,ESP32-C3_SUPERMINI_TH,

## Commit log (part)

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2025-04-03 add more instructions and approved parts :fire: :fire: :fire: :fire: :fire:
2025-04-03 example submission :fire:
2025-04-04 Add design files
2025-04-04 Forgor to upload the source file :3
2025-04-05 Added BOM and gerbers
2025-04-05 Added PixelDoro
2025-04-05 add initial files
2025-04-05 orginization
2025-04-05 Rename submissions/chrismas_tree.kicad_pro to submissions/src/chrismas_tree.kicad_pro
2025-04-05 Rename submissions/gerber.zip to submissions/production/gerber.zip
2025-04-05 Rename pixeldust.pdf to schematic.pdf
2025-04-05 Rename CPL-pixeldust-tutorial.csv to CPL-pixeldust-tutorial.csv
2025-04-05 Rename submissions/production/gerber.zip to submissions/sahils_christmas_tree/production/gerber.zip
2025-04-05 Rename submissions/src/chrismas_tree.kicad_pro to submissions/sahils_christmas_tree/src/chrismas_tree.kicad_pro
2025-04-05 Rename submissions/schematic.pdf to submissions/sahils_christmas_tree/schematic.pdf
2025-04-06 add lumicoaster
2025-04-06 rename
2025-04-06 fix oopsie
2025-04-06 oops! wrong sketch.ino
2025-04-06 Rename pixeldust.pdf to christmas_tree.pdf
2025-04-06 Rename christmas_tree.pdf to pixeldust.pdf
2025-04-06 Rename submissions/sahils_christmas_tree/production/sketch.ino to submissions/sahils_christmas_tree/production/wokwi/sketch.ino
2025-04-07 added logos to back silkscreen
2025-04-07 added username and removed some silkscreen clutter
2025-04-07 Add the NeoPOV
2025-04-07 update some stuff in guide and req, add faq and resources page
2025-04-07 improve submission guidelines
2025-04-08 Rename submissions/3dboardtemplate.stl to submissions/3XAY_Lightbox/3dboardtemplate.stl
2025-04-08 Rename submissions/board.pcb3d to submissions/3XAY_Lightbox/board.pcb3d
2025-04-08 Rename submissions/code.zip to submissions/3XAY_Lightbox/code.zip
2025-04-08 Rename submissions/3XAY_Lightbox/LightBoxDesign.jpg to submissions/3XAY_Lightbox/Pictures/LightBoxDesign.jpg
2025-04-08 Rename submissions/3XAY_Lightbox/LightBoxWiring.jpg to submissions/3XAY_Lightbox/Pictures/LightBoxWiring.jpg
2025-04-09 Rename submissions/3XAY_Lightbox/lightbox.kicad_pro to submissions/3XAY_Lightbox/src/lightbox.kicad_pro
2025-04-09 Add LightRay
2025-04-09 Round Corners
2025-04-10 Make traces thicker
2025-04-10 Add lightbulb files
2025-04-11 Create a
2025-04-11 Add BOM
2025-04-11 Add schematic
2025-04-11 Create src/
2025-04-11 Add src files
2025-04-11 Create folder src/
2025-04-11 Create folder production/
2025-04-11 more info on submitting
2025-04-11 Replace submissions/TempMatrix/schematic.pdf
2025-04-11 Replace schematic.pdf
2025-04-12 boom
2025-04-12 Start creating the README for Neopixel Themometer
2025-04-12 Add sections
2025-04-12 Talk about the design process
2025-04-12 Mockup image
2025-04-12 Rename submissions/3XAY_Lightbox/Schematic.jpg to submissions/3XAY_Lightbox/Pictures/Schematic.jpg
2025-04-12 draft irl-raver submission
2025-04-13 split pdf
2025-04-13 add: @turtureanu's LED glasses
2025-04-13 Rename folder from Neopixel to NeoPixel
2025-04-13 Add images!
2025-04-13 Add BOM
    This took a while...
2025-04-13 Add exported files
2025-04-13 added src file
2025-04-13 added schem and bom
2025-04-13 added geber, cpl and bom
2025-04-13 image of pcb
2025-04-13 Rename image.png to pcb_front.png
2025-04-13 added schem file
2025-04-13 Delete submissions/duykhanh09103_PixelPad/images/image.png
    wth github why is it uploading the same img
2025-04-13 added schem img
2025-04-13 Delete submissions/duykhanh09103_PixelPad/images/image.png
    i giveup
2025-04-13 ty github codespace
2025-04-13 + Wokwi link
2025-04-13 Add AHT20 code
2025-04-13 Add shiekah-eye
2025-04-13 Add GIF_Matrix
2025-04-14 Filled out PR
2025-04-14 Fixed some PR issues
2025-04-14 Filled out my PR
2025-04-14 added pixel-dongle
2025-04-14 Update README.md -- person20020
2025-04-14 Update README.md -- added bom
2025-04-14 added schematic pdf
2025-04-14 Add the stages of simplifying
2025-04-14 add capacitor
2025-04-14 final changes
2025-04-14 credits to XKCD
2025-04-16 Create submission folder
2025-04-16 Create src directory
2025-04-16 new file: submissions/Arrow/BOM-pixeldust-tutorial.csv new file: submissions/Arrow/README.md new file: submissions/Arrow/production/Gerber.zip new file: submissions/Arrow/production/main.c new file: 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
2025-04-16 Added all the things
2025-04-17 Added pyramid of brightness
2025-04-17 fix files deleted: submissions/moodmatrix/PCB renamed: submissions/moodmatrix/trinkey-.zip -> submissions/moodmatrix/PCB/trinkey-.zip renamed: submissions/moodmatrix/trinkey.kicad_pcb -> submissions/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
2025-04-17 Add Kicad files
2025-04-17 Removed unnecessary libraries
2025-04-18 Create placeholder
2025-04-18 Add anipixel
2025-04-18 Add board firmware
2025-04-18 Create img folder
2025-04-18 Create folder for my footprints
    I couldn´t find any, so i had to make my own (for example, for the Adafruit AHT20 board)
2025-04-18 add source files (PCB, schematic)
2025-04-18 Add custom footprints
2025-04-18 Add gerber+drill zip file
2025-04-18 fix filepaths
2025-04-18 Add description and BoM to readme
2025-04-18 Add design story to readme
2025-04-18 Upload related images
2025-04-18 Add images to readme
2025-04-18 Rename for readme
2025-04-18 Add screenshot of AHT20 footprint
2025-04-18 Add footprint to readme
2025-04-19 Add schematic pdf
2025-04-19 Change decoupling cap
2025-04-19 update BOM
2025-04-19 Update BOM-TempMatrix.csv to add WW LEDs
2025-04-19 Update README.md to add Warm White LEDs and hotplate requirement instead of iron
2025-04-20 Add wokwi link to readme
    https://wokwi.com/projects/428760578626492417
2025-04-20 fix top table
    hopefully, idk what is a "yaml error at line 5 column 9"
2025-04-21 deleted: submissions/Arrow/BOM-pixeldust-tutorial.csv modified: submissions/Arrow/README.md deleted: submissions/Arrow/production/main.c new file: submissions/Arrow/production/main.py modified: submi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
2025-04-21 Use esp32
2025-04-21 moved the file to be in the right folder
2025-04-21 add main.c
2025-04-21 Add code
2025-04-22 fix i2c initiation
    board->busio so that i can use my selected pins
2025-04-22 Added main.c
2025-04-23 add README.md
2025-04-23 add gerber, bom
2025-04-23 add pdf
2025-04-23 fix Slack ID in README
2025-04-23 add main.py
2025-04-23 Add Audrino/C source code
2025-04-25 remove some unnecessary files deleted: submissions/PixelDoro/assets/libraries/OPL_Kicad_Library/Seeed Studio XIAO Series Library/XIAO-Add-On.kicad_mod deleted: submissions/PixelDoro/assets/libraries/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
2025-04-25 add fw
2025-04-25 added code folder
2025-04-26 my pcb
2025-04-26 with vid now
2025-04-26 readme fixx
2025-04-26 rm backups
2025-04-26 fix image links (add schematic, pcb, diagram), fix spelling error
2025-04-26 Update README.md (add quotes to Jekyll block)
2025-04-26 Update README.md (fix wokwi link in block)
2025-04-26 Update README.md (further fix block wokwi link)
2025-04-26 fixed many
2025-04-26 pics
2025-04-26 fiixed all
2025-04-26 rm backup
2025-04-27 updated submisssion Made sure submisssion met the standards for submitting Made changes to pcb so it would actually work
2025-04-27 updated photos
2025-04-27 fix table
